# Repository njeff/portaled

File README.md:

# PortaLED

This is essentially a flashlight I designed because I wanted to use some free parts from TI. This uses the LM3410 driver to boost the voltage of the LiPo battery and drive the LEDs at a constant current. I have it setup to drive two 3W LEDs in series at approximately 630 mA (at max brightness). 

An ATTiny85 is used to control the whole system, and push button is used input.

This repository has the C firmware code and the KiCAD PCB design files. The PCB in the *const-led* folder has an additional battery gauge IC (MAX17043) for more accurate battery level tracking, and the one in *const-led-ez* doesn't. I only made the *ez* variant.

### Features
 - 8 brightness levels (maybe adjusted to be a linear/exponential ramp)
 - Battery level blink out (blinks out the volts, then tenth of a volt)
 - Low voltage/battery level cutoff
 - USB LiPo charging circuit

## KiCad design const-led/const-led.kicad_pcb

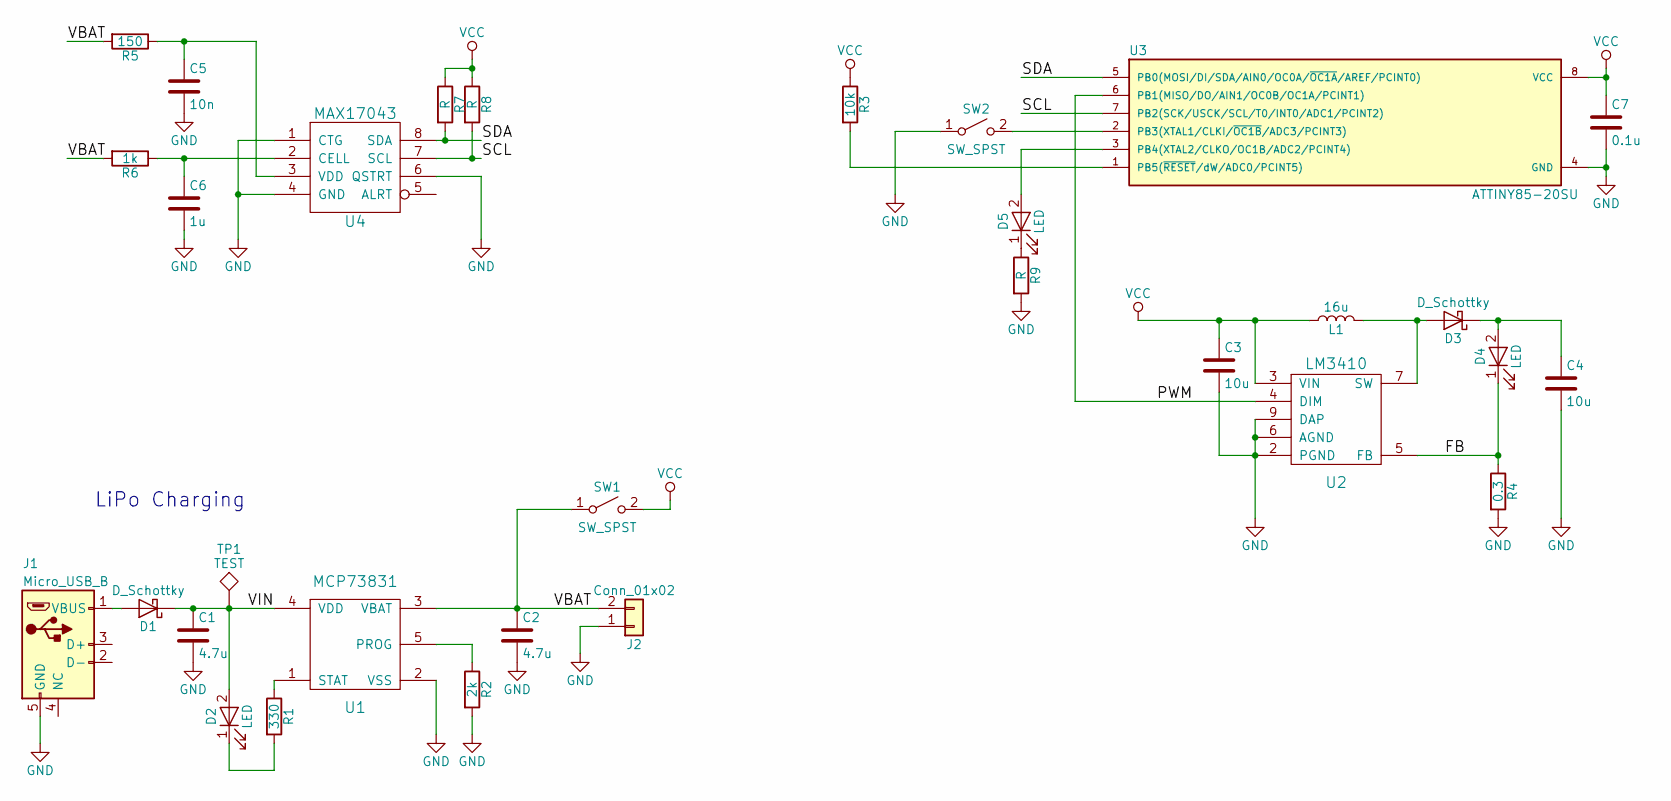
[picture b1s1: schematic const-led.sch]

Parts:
C1, C2: 4.7u; C_0603
C3, C4: 10u; C_1206
C5: 10n; C_0603
C6: 1u; C_0805
C7: 0.1u; C_0805
D1, D3: D_Schottky; D_SMA
D2, D5: LED; LED_0603
D4: LED; Pin_Header_Straight_1x02_Pitch2.54mm
J1: Micro_USB_B; Micro_USB_B_NH
J2: Conn_01x02; JST-PH-2
L1: 16u; muRata_L
R1: 330; R_0603
R2: 2k; R_0603
R3: 10k; R_0603
R4: 0.3; R_0805
R5: 150; R_0603
R6: 1k; R_0603
R7, R8, R9: R; R_0603
SW1, SW2: SW_SPST; Pin_Header_Straight_1x02_Pitch1.00mm
TP1: TEST; Measurement_Point_Round-SMD-Pad_Small
U1: MCP73831; SOT-23-5
U2: LM3410; MSOP-8-1EP_3x3mm_Pitch0.65mm
U3: ATTINY85-20SU; SOIC-8_8x5.25x1.27mm
U4: MAX17043; TDFN-8_2x3x0.75mm

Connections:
/FB: D4.1 (K), R4.1, U2.5 (FB)
/PWM: U2.4 (DIM), U3.6 (PB1(MISO/DO/AIN1/OC0B/OC1A/PCINT1))
/SCL: R8.2, U3.7 (PB2(SCK/USCK/SCL/T0/INT0/ADC1/PCINT2)), U4.7 (SCL)
/SDA: R7.2, U3.5 (PB0(MOSI/DI/SDA/AIN0/OC0A/~OC1A~/AREF/P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), U4.8 (SDA)
/VBAT: C2.1, J2.2, R5.2, R6.2, SW1.1 (A), U1.3 (VBAT)
/VIN: C1.1, D1.1 (K), D2.2 (A), TP1.1, U1.4 (VDD)
GND: C1.2, C2.2, C3.2, C4.2, C5.2, C6.2, C7.2, J1.5 (GND), J2.1, R2.2, R4.2, R9.2, SW2.1 (A), U1.2 (VSS), U2.2 (PGND), U2.6 (AGND), U2.9 (DAP), U3.4 (GND), U4.1 (CTG), U4.4 (GND), U4.6 (QSTRT)
unnamed: C4.1, D3.1 (K), D4.2 (A)
unnamed: C5.1, R5.1, U4.3 (VDD)
unnamed: C6.1, R6.1, U4.2 (CELL)
unnamed: D1.2 (A), J1.1 (VBUS)
unnamed: D2.1 (K), R1.2
unnamed: D3.2 (A), L1.2, U2.7 (SW)
unnamed: D5.1 (K), R9.1
unnamed: D5.2 (A), U3.3 (PB4(XTAL2/CLKO/OC1B/ADC2/PCINT4))
unnamed: R1.1, U1.1 (STAT)
unnamed: R2.1, U1.5 (PROG)
unnamed: R3.2, U3.1 (PB5(~RESET~/dW/ADC0/PCINT5))
unnamed: SW2.2 (B), U3.2 (PB3(XTAL1/CLKI/~OC1B~/ADC3/PCINT3))
VCC: C3.1, C7.1, L1.1, R3.1, R7.1, R8.1, SW1.2 (B), U2.3 (VIN), U3.8 (VCC)

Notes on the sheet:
LiPo Charging

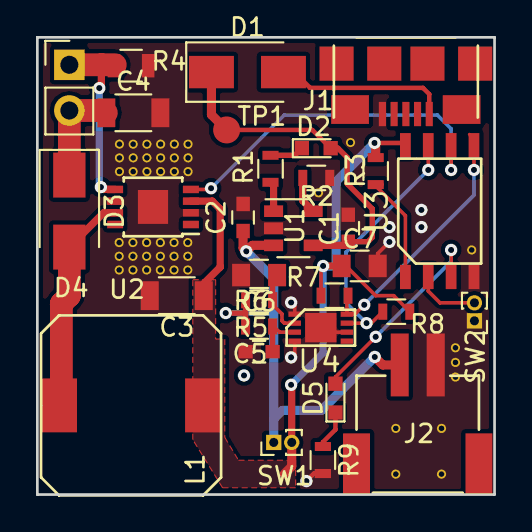
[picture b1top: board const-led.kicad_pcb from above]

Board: 2 copper layers, 25.4 x 25.4 mm, 31 parts (0 on the bottom side), 20 nets.

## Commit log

2018-02-21 Added millis and PWM
2018-02-25 Added (blocking) battery read out; still working on low PWM levels
2018-02-26 Changes now occur on button release
2018-02-26 Added README
2018-05-02 Case parts
2018-05-04 Rev2
